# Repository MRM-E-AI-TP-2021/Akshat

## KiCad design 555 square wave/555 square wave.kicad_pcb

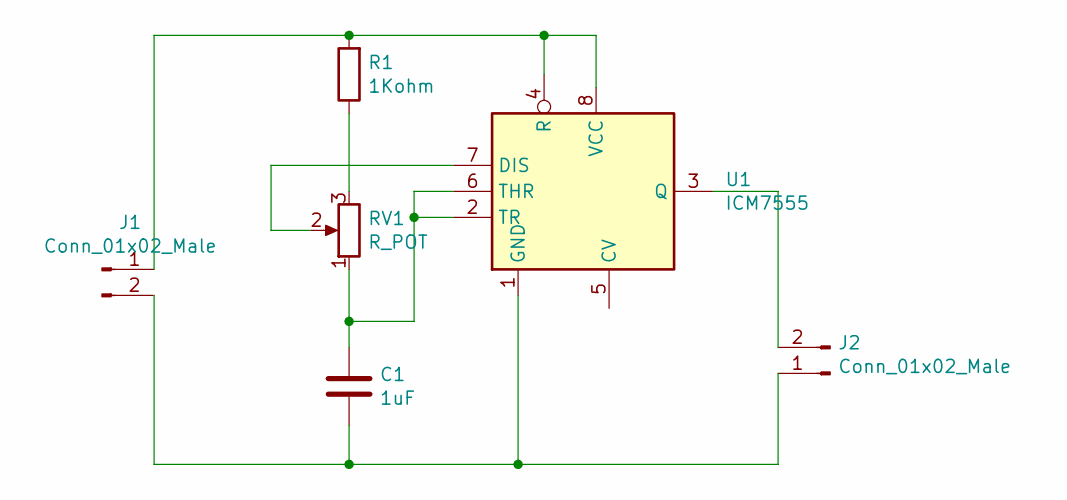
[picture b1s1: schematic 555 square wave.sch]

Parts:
C1: 1uF; C_Radial_D8.0mm_H11.5mm_P3.50mm
J1, J2: Conn_01x02_Male; PinHeader_1x02_P2.00mm_Vertical
R1: 1Kohm; R_Axial_DIN0309_L9.0mm_D3.2mm_P20.32mm_Horizontal
RV1: R_POT; Potentiometer_Bourns_3339P_Vertical
U1: ICM7555; 555sqwave

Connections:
unnamed: C1.1, RV1.1, U1.2 (TR), U1.6 (THR)
unnamed: C1.2, J1.2, J2.1, U1.1 (GND)
unnamed: J1.1, R1.2, U1.4 (R), U1.8 (VCC)
unnamed: J2.2, U1.3 (Q)
unnamed: R1.1, RV1.3
unnamed: RV1.2, U1.7 (DIS)

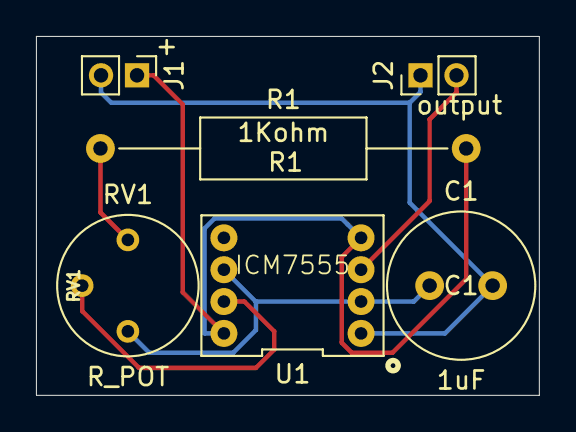
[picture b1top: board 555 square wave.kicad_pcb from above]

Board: 2 copper layers, 27.9 x 19.9 mm, 6 parts (0 on the bottom side), 6 nets.

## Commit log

2019-12-30 Create SerialPrint
2019-12-31 Create JoystickWithLED
2020-01-07 Create joystickfinal
